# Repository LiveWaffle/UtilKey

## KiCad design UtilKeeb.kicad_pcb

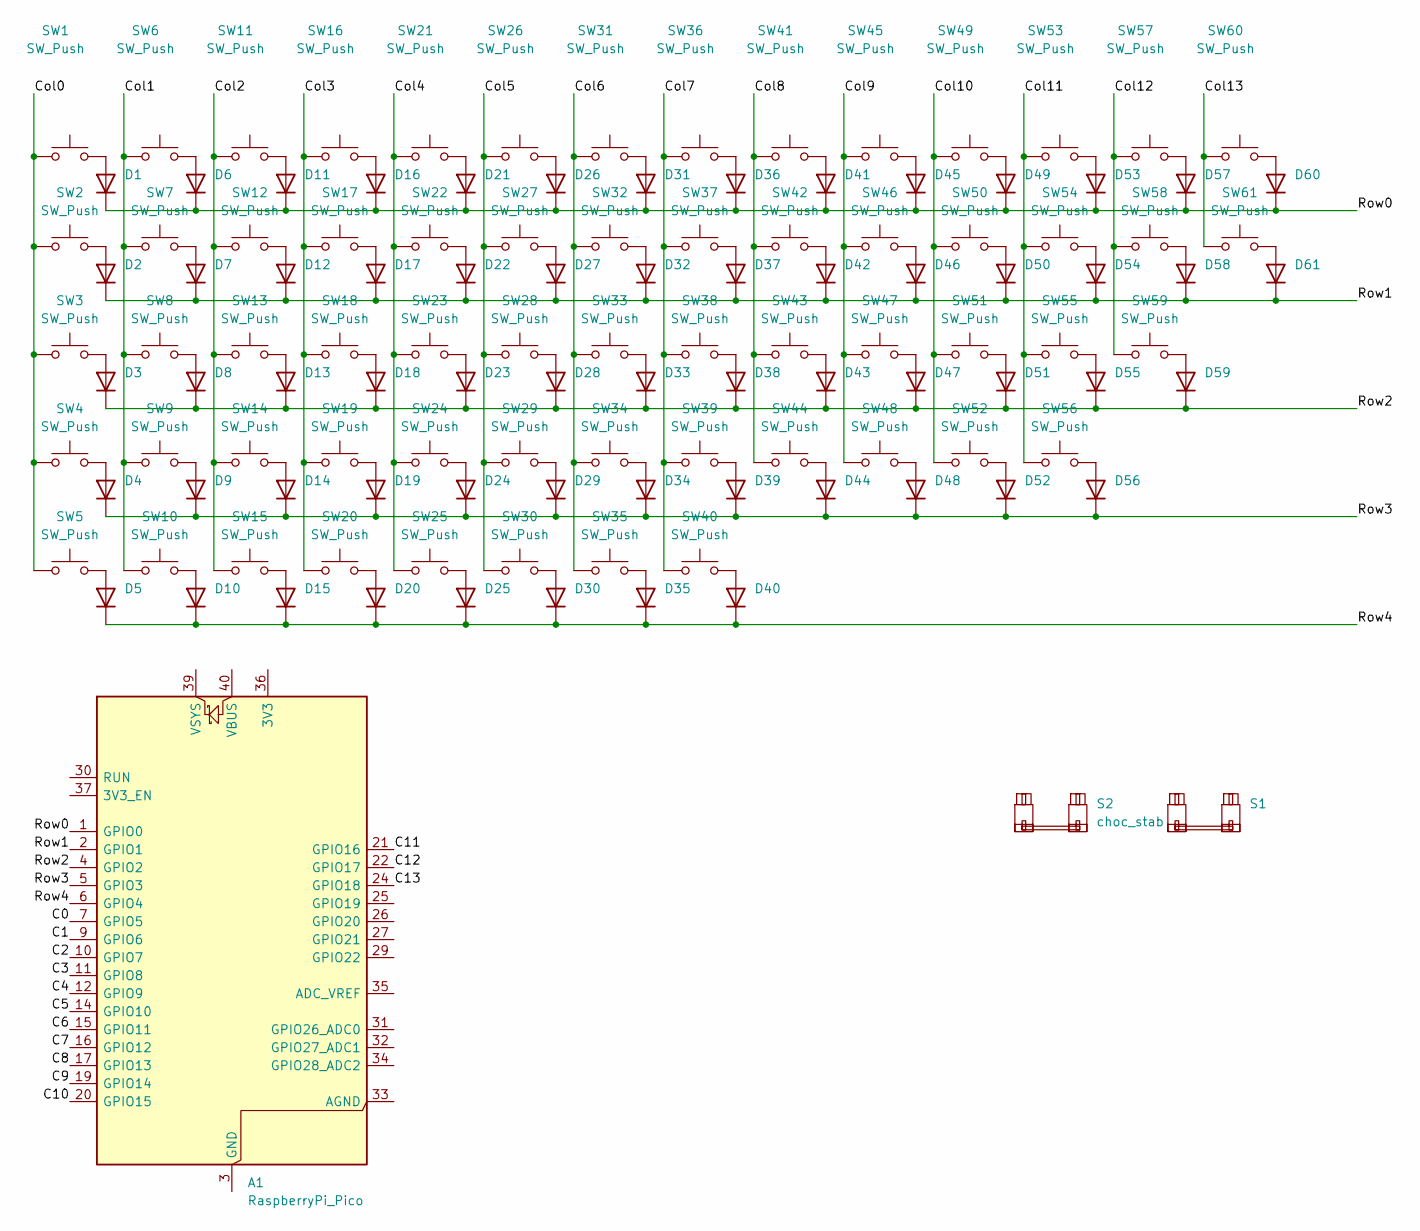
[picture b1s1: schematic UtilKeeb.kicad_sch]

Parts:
A1: RaspberryPi_Pico; RaspberryPi_Pico_Common_Unspecified
D1, D2, D3, D4, D5, D6, D7, D8, D9, D10, D11, D12, D13, D14, D15, D16, D17, D18, D19, D20, D21, D22, D23, D24, D25, D26, D27, D28, D29, D30, D31, D32, D33, D34, D35, D36, D37, D38, D39, D40, D41, D42, D43, D44, D45, D46, D47, D48, D49, D50, D51, D52, D53, D54, D55, D56, D57, D58, D59, D60, D61: 1N4148; D_DO-35_SOD27_P7.62mm_Horizontal
S1: MX_stab; STAB_MX_6.25u
S2: choc_stab; STAB_choc_2u
SW1, SW6, SW7, SW8, SW9, SW11, SW12, SW13, SW15, SW16, SW17, SW18, SW19, SW20, SW21, SW22, SW23, SW24, SW26, SW27, SW28, SW29, SW31, SW32, SW33, SW34, SW36, SW37, SW38, SW39, SW41, SW42, SW43, SW44, SW45, SW46, SW47, SW48, SW49, SW50, SW51, SW52, SW53, SW54, SW55, SW56, SW57, SW58, SW59, SW60: SW_Push; SW_MX_1u
SW2: SW_Push; SW_MX_1.5u
SW3: SW_Push; SW_MX_1.75u
SW4: SW_Push; STAB_MX_2.25u
SW5: SW_Push; SW_Cherry_MX_1.25u_PCB
SW10, SW14, SW25, SW30, SW35, SW40: SW_Push; SW_MX_1.25u
SW61: SW_Push; STAB_MX_2u

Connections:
/C0: A1.7 (GPIO5)
/C1: A1.9 (GPIO6)
/C2: A1.10 (GPIO7)
/C3: A1.11 (GPIO8)
/C4: A1.12 (GPIO9)
/C5: A1.14 (GPIO10)
/C6: A1.15 (GPIO11)
/C7: A1.16 (GPIO12)
/C8: A1.17 (GPIO13)
/C9: A1.19 (GPIO14)
/C10: A1.20 (GPIO15)
/C11: A1.21 (GPIO16)
/C12: A1.22 (GPIO17)
/C13: A1.24 (GPIO18)
/Col0: SW1.1, SW2.1, SW3.1, SW4.1, SW5.1
/Col1: SW6.1, SW7.1, SW8.1, SW9.1, SW10.1
/Col2: SW11.1, SW12.1, SW13.1, SW14.1, SW15.1
/Col3: SW16.1, SW17.1, SW18.1, SW19.1, SW20.1
/Col4: SW21.1, SW22.1, SW23.1, SW24.1, SW25.1
/Col5: SW26.1, SW27.1, SW28.1, SW29.1, SW30.1
/Col6: SW31.1, SW32.1, SW33.1, SW34.1, SW35.1
/Col7: SW36.1, SW37.1, SW38.1, SW39.1, SW40.1
/Col8: SW41.1, SW42.1, SW43.1, SW44.1
/Col9: SW45.1, SW46.1, SW47.1, SW48.1
/Col10: SW49.1, SW50.1, SW51.1, SW52.1
/Col11: SW53.1, SW54.1, SW55.1, SW56.1
/Col12: SW57.1, SW58.1, SW59.1
/Col13: SW60.1, SW61.1
/Row0: A1.1 (GPIO0), D1.1 (K), D6.1 (K), D11.1 (K), D16.1 (K), D21.1 (K), D26.1 (K), D31.1 (K), D36.1 (K), D41.1 (K), D45.1 (K), D49.1 (K), D53.1 (K), D57.1 (K), D60.1 (K)
/Row1: A1.2 (GPIO1), D2.1 (K), D7.1 (K), D12.1 (K), D17.1 (K), D22.1 (K), D27.1 (K), D32.1 (K), D37.1 (K), D42.1 (K), D46.1 (K), D50.1 (K), D54.1 (K), D58.1 (K), D61.1 (K)
/Row2: A1.4 (GPIO2), D3.1 (K), D8.1 (K), D13.1 (K), D18.1 (K), D23.1 (K), D28.1 (K), D33.1 (K), D38.1 (K), D43.1 (K), D47.1 (K), D51.1 (K), D55.1 (K), D59.1 (K)
/Row3: A1.5 (GPIO3), D4.1 (K), D9.1 (K), D14.1 (K), D19.1 (K), D24.1 (K), D29.1 (K), D34.1 (K), D39.1 (K), D44.1 (K), D48.1 (K), D52.1 (K), D56.1 (K)
/Row4: A1.6 (GPIO4), D5.1 (K), D10.1 (K), D15.1 (K), D20.1 (K), D25.1 (K), D30.1 (K), D35.1 (K), D40.1 (K)
unnamed: A1.3 (GND), A1.8 (GND), A1.13 (GND), A1.18 (GND), A1.23 (GND), A1.28 (GND), A1.38 (GND)
unnamed: D1.2 (A), SW1.2
unnamed: D2.2 (A), SW2.2
unnamed: D3.2 (A), SW3.2
unnamed: D4.2 (A), SW4.2
unnamed: D5.2 (A), SW5.2
unnamed: D6.2 (A), SW6.2
unnamed: D7.2 (A), SW7.2
unnamed: D8.2 (A), SW8.2
unnamed: D9.2 (A), SW9.2
unnamed: D10.2 (A), SW10.2
unnamed: D11.2 (A), SW11.2
unnamed: D12.2 (A), SW12.2
unnamed: D13.2 (A), SW13.2
unnamed: D14.2 (A), SW14.2
unnamed: D15.2 (A), SW15.2
unnamed: D16.2 (A), SW16.2
unnamed: D17.2 (A), SW17.2
unnamed: D18.2 (A), SW18.2
unnamed: D19.2 (A), SW19.2
unnamed: D20.2 (A), SW20.2
unnamed: D21.2 (A), SW21.2
unnamed: D22.2 (A), SW22.2
unnamed: D23.2 (A), SW23.2
unnamed: D24.2 (A), SW24.2
unnamed: D25.2 (A), SW25.2
unnamed: D26.2 (A), SW26.2
unnamed: D27.2 (A), SW27.2
unnamed: D28.2 (A), SW28.2
unnamed: D29.2 (A), SW29.2
unnamed: D30.2 (A), SW30.2
unnamed: D31.2 (A), SW31.2
unnamed: D32.2 (A), SW32.2
unnamed: D33.2 (A), SW33.2
unnamed: D34.2 (A), SW34.2
unnamed: D35.2 (A), SW35.2
unnamed: D36.2 (A), SW36.2
unnamed: D37.2 (A), SW37.2
unnamed: D38.2 (A), SW38.2
unnamed: D39.2 (A), SW39.2
unnamed: D40.2 (A), SW40.2
unnamed: D41.2 (A), SW41.2
unnamed: D42.2 (A), SW42.2
unnamed: D43.2 (A), SW43.2
unnamed: D44.2 (A), SW44.2
unnamed: D45.2 (A), SW45.2
unnamed: D46.2 (A), SW46.2
unnamed: D47.2 (A), SW47.2
unnamed: D48.2 (A), SW48.2
unnamed: D49.2 (A), SW49.2
unnamed: D50.2 (A), SW50.2
unnamed: D51.2 (A), SW51.2
unnamed: D52.2 (A), SW52.2
unnamed: D53.2 (A), SW53.2
unnamed: D54.2 (A), SW54.2
unnamed: D55.2 (A), SW55.2
unnamed: D56.2 (A), SW56.2
unnamed: D57.2 (A), SW57.2
unnamed: D58.2 (A), SW58.2
unnamed: D59.2 (A), SW59.2
unnamed: D60.2 (A), SW60.2
unnamed: D61.2 (A), SW61.2

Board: 2 copper layers, 126 parts (0 on the bottom side), 79 nets, no tracks yet.

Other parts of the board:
S3: choc_stab; STAB_MX_P_6.25u
